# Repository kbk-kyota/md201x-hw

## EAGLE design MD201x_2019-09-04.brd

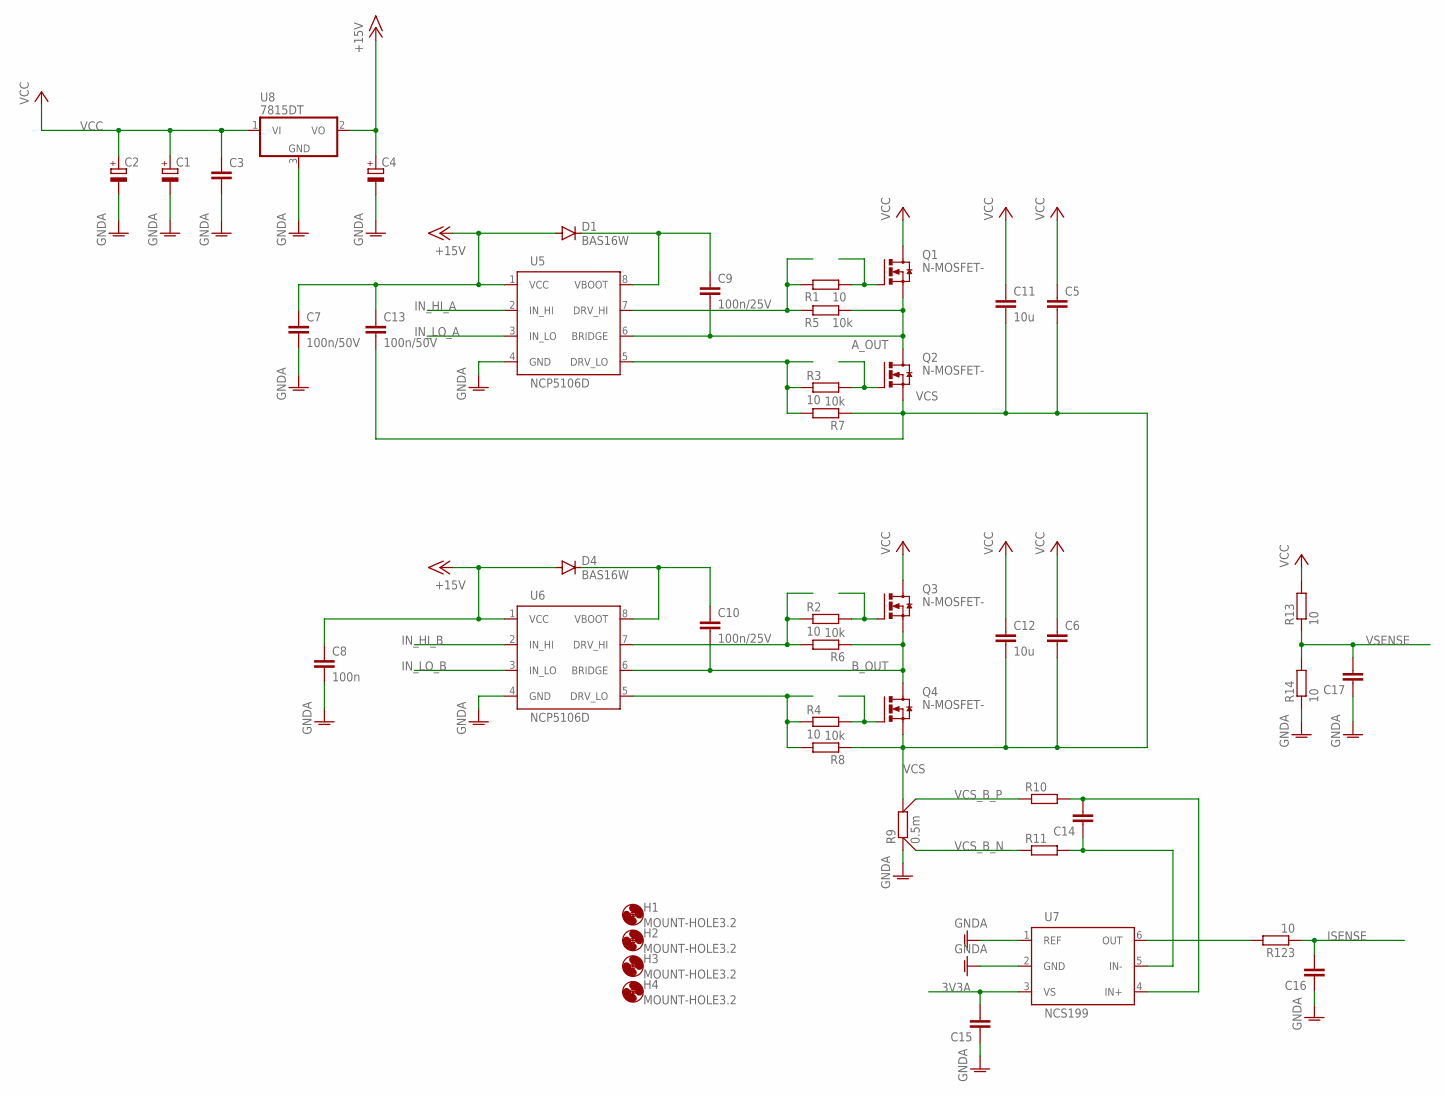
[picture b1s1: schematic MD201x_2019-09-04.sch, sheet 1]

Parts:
C1, C2: CPOL-EUE5-10.5; E5-10,5
C3, C5, C6, C14, C15, C16, C17: C-EUC0603; C0603
C4: CPOL-EUE2.5-5; E2,5-5
C7, C13: 100n/50V; C0603
C8: 100n; C0603
C9, C10: 100n/25V; C0603
C11, C12: 10u; C1210
D1, D4: BAS16W; SOD323-R
H1, H2, H3, H4: MOUNT-HOLE3.2; 3,2
Q1, Q2, Q3, Q4: N-MOSFET-; SOT669
R1, R2, R3, R4, R13, R14, R123: 10; R0603
R5, R6, R7, R8: 10k; R0603
R9: 0.5m; CSS2H-2512
R10, R11: R-EU_R0603; R0603
U5, U6: NCP5106D; SOIC127P600X175-8
U7: NCS199; SOT65P210X110-6
U8: 7815DT; TO252

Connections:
3V3A: C15.2, U7.3 (VS); also elsewhere on the board
+15V: C4.+, C7.1, C8.1, C13.1, D1.A, D4.A, U5.1 (VCC), U6.1 (VCC), U8.2 (VO); also elsewhere on the board
A_OUT: C9.2, Q1.1 (SOURCE), Q1.2 (SOURCE), Q1.3 (SOURCE), Q2.5 (DRAIN), R5.1, U5.6 (BRIDGE)
B_OUT: C10.2, Q3.1 (SOURCE), Q3.2 (SOURCE), Q3.3 (SOURCE), Q4.5 (DRAIN), R6.1, U6.6 (BRIDGE)
GNDA: C1.-, C2.-, C3.2, C4.-, C7.2, C8.2, C15.1, C16.1, C17.1, R9.1$1 (1), R9.1$2 (1), R14.1, U5.4 (GND), U6.4 (GND), U7.1 (REF), U7.2 (GND), U8.3 (GND); also elsewhere on the board
IN_HI_A: U5.2 (IN_HI); also elsewhere on the board
IN_HI_B: U6.2 (IN_HI); also elsewhere on the board
IN_LO_A: U5.3 (IN_LO); also elsewhere on the board
IN_LO_B: U6.3 (IN_LO); also elsewhere on the board
ISENSE: C16.2, R123.1; also elsewhere on the board
unnamed: R1.1, R5.2, U5.7 (DRV_HI)
unnamed: R2.1, R6.2, U6.7 (DRV_HI)
unnamed: Q1.4 (GATE), R1.2
unnamed: R4.1, R8.2, U6.5 (DRV_LO)
unnamed: R123.2, U7.6 (OUT)
unnamed: R3.1, R7.2, U5.5 (DRV_LO)
unnamed: Q3.4 (GATE), R2.2
unnamed: C14.2, R10.2, U7.4 (IN+)
unnamed: C14.1, R11.2, U7.5 (IN-)
unnamed: Q2.4 (GATE), R3.2
unnamed: Q4.4 (GATE), R4.2
unnamed: C10.1, D4.C, U6.8 (VBOOT)
unnamed: C9.1, D1.C, U5.8 (VBOOT)
VCC: C1.+, C2.+, C3.1, C5.1, C6.1, C11.1, C12.1, Q1.5 (DRAIN), Q3.5 (DRAIN), R13.2, U8.1 (VI)
VCS: C5.2, C6.2, C11.2, C12.2, C13.2, Q2.1 (SOURCE), Q2.2 (SOURCE), Q2.3 (SOURCE), Q4.1 (SOURCE), Q4.2 (SOURCE), Q4.3 (SOURCE), R7.1, R8.1, R9.2$1 (2), R9.2$2 (2)
VCS_B_N: R9.1S, R11.1
VCS_B_P: R9.2S, R10.1
VSENSE: C17.2, R13.1, R14.2; also elsewhere on the board

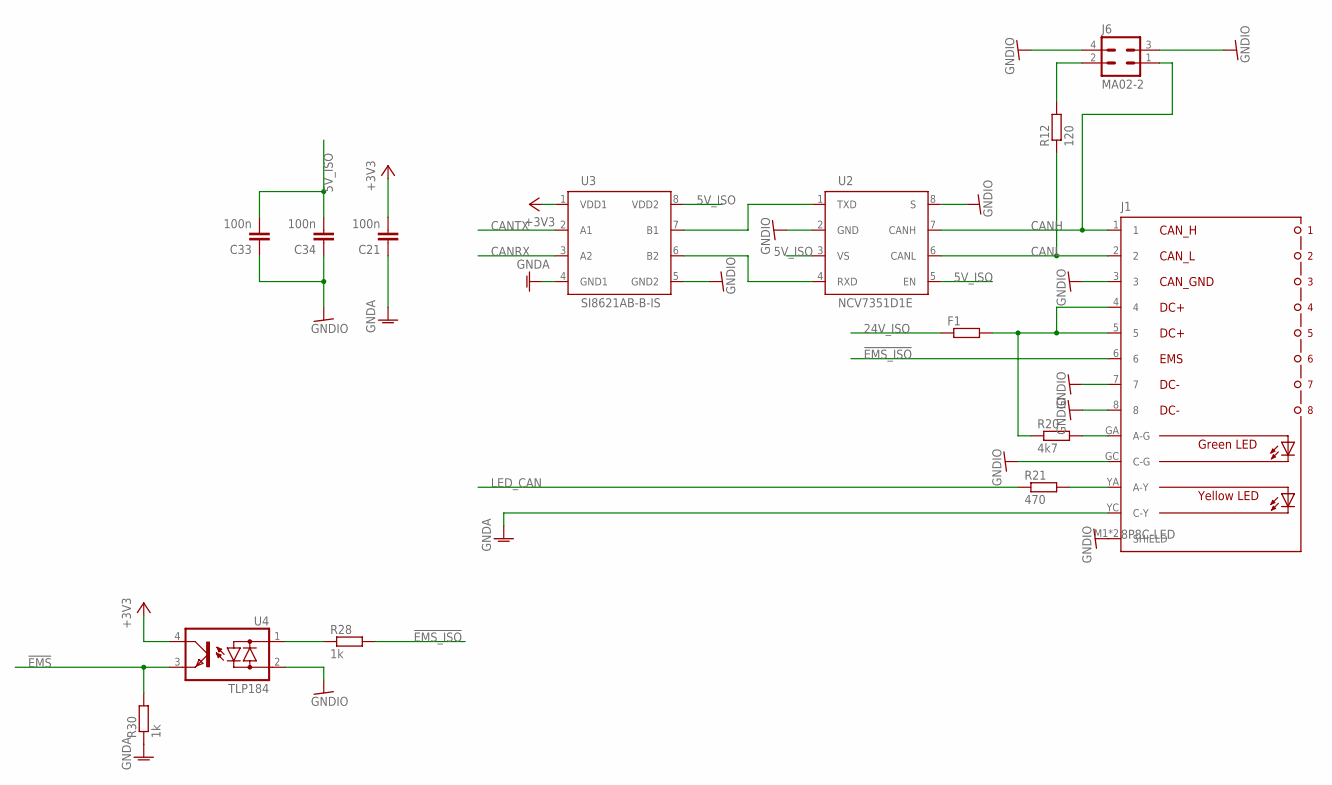
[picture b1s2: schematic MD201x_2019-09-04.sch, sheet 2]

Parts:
C21, C34: 100n; C0603
C33: 100n; C0805
F1: R-EU_R1206; R1206
J1: 8P8C-LED
J6: MA02-2; MA02-2W
R12: 120; R0603
R20: 4k7; R0603
R21: 470; R0603
R28, R30: 1k; R0603
U2: NCV7351D1E; SO08
U3: SI8621AB-B-IS; SO08
U4: TLP184; 11-4M1S

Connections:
5V_ISO: C33.2, C34.2, U2.3 (VS), U2.5 (EN), U3.8 (VDD2); also elsewhere on the board
24V_ISO: F1.1; also elsewhere on the board
!EMS: R30.2, U4.3 (E); also elsewhere on the board
!EMS_ISO: J1.6, R28.2
+3V3: C21.2, U3.1 (VDD1), U4.4 (C); also elsewhere on the board
CANH: J1.1, J6.1, U2.7 (CANH)
CANL: J1.2, R12.1, U2.6 (CANL)
CANRX: U3.3 (A2); also elsewhere on the board
CANTX: U3.2 (A1); also elsewhere on the board
GNDA: C21.1, J1.YC (C-Y), R30.1, U3.4 (GND1); also elsewhere on the board
GNDIO: C33.1, C34.1, J1.3, J1.7, J1.8, J1.GC (C-G), J1.M1 (SHIELD), J1.M2 (SHIELD), J6.3, J6.4, U2.2 (GND), U2.8 (S), U3.5 (GND2), U4.2 (AC2); also elsewhere on the board
LED_CAN: R21.1; also elsewhere on the board
unnamed: F1.2, J1.4, J1.5, R20.1
unnamed: J6.2, R12.2
unnamed: J1.GA (A-G), R20.2
unnamed: J1.YA (A-Y), R21.2
unnamed: U2.1 (TXD), U3.7 (B1)
unnamed: U2.4 (RXD), U3.6 (B2)
unnamed: R28.1, U4.1 (AC1)

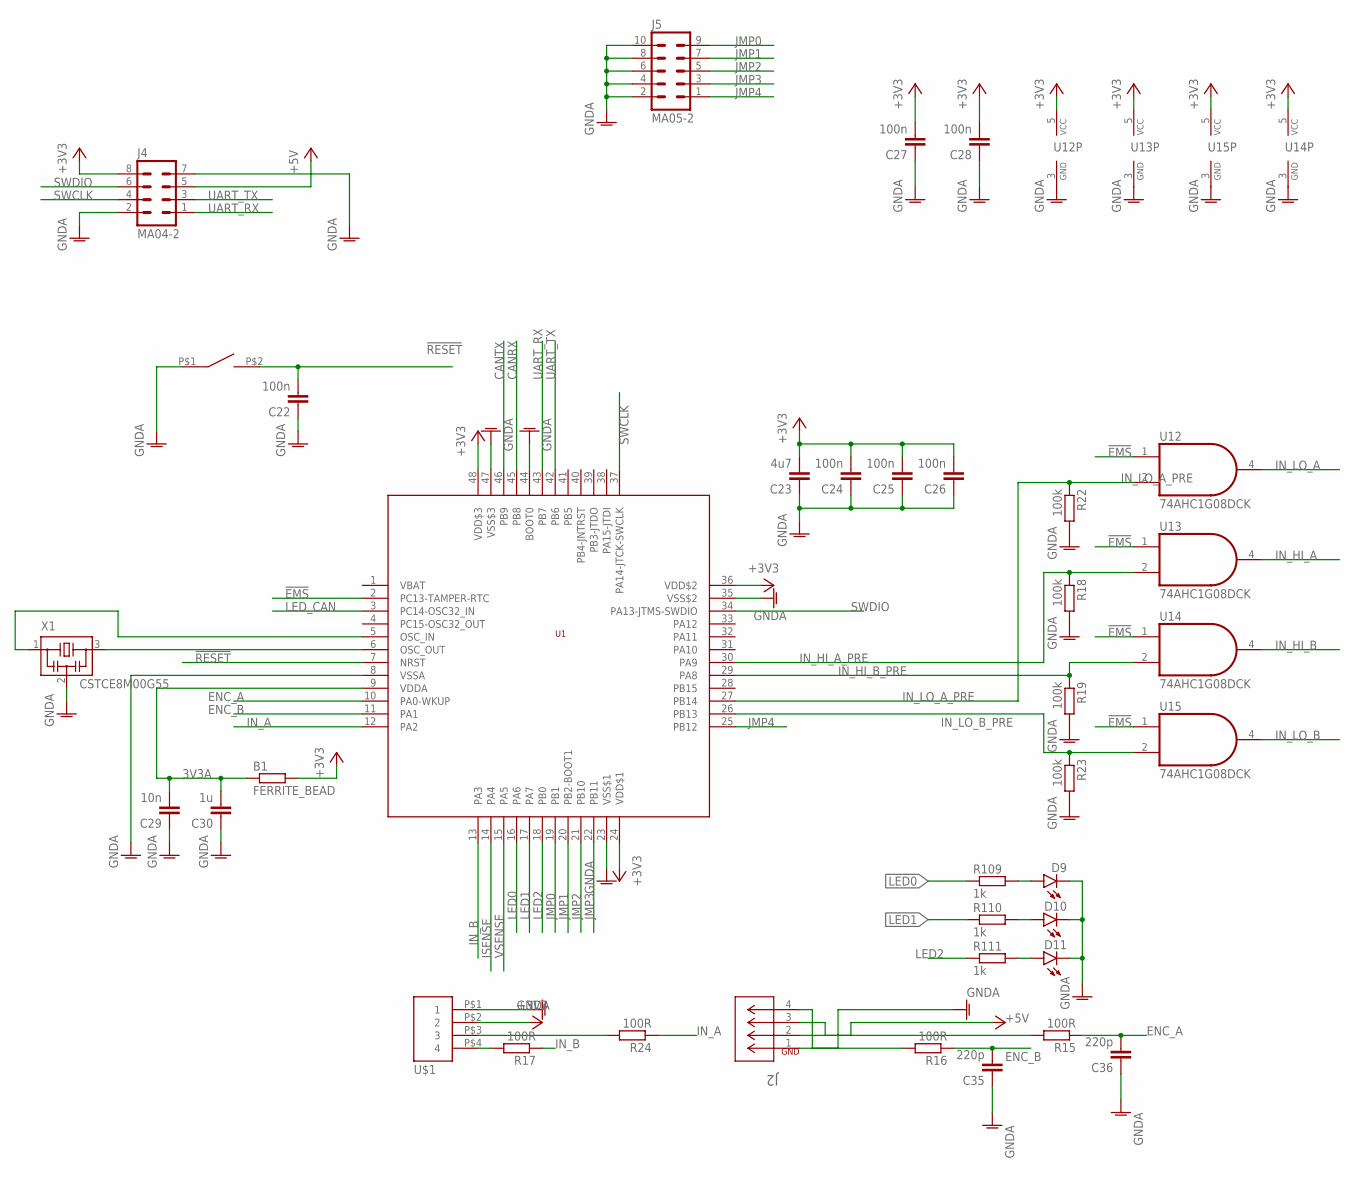
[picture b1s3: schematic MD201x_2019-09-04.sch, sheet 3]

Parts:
B1: FERRITE_BEAD; R0603
C22, C24, C25, C26, C27, C28: 100n; C0603
C23: 4u7; C0805
C29: 10n; C0603
C30: 1u; C0603
C35, C36: 220p; C0603
D9, D10, D11: LEDCHIPLED_0805; CHIPLED_0805
J2: 1744426-4; CONN4_1744426-4
J4: MA04-2; MA04-2W
J5: MA05-2; MA05-2W
R15, R16, R17, R24: 100R; R0603
R18, R19, R22, R23: 100k; R0603
R109, R110, R111: 1k; R0603
S1: SWITCH_TACTILETOP; SWITCH_TACTILE_3X6
U1: STM32F103C8; LQFP48
U12, U13, U14, U15: 74AHC1G08DCK; SC70-5
U$1: XH-4-SIDE; CON-XH-4-SIDE
X1: CSTCE8M00G55

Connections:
3V3A: B1.1, C29.2, C30.2, U1.9 (VDDA); also elsewhere on the board
!EMS: U1.2 (PC13-TAMPER-RTC), U12.1 (I0), U13.1 (I0), U14.1 (I0), U15.1 (I0); also elsewhere on the board
!RESET: C22.2, S1.P$2 (2), U1.7 (NRST)
+3V3: B1.2, C23.2, C24.2, C25.2, C26.2, C27.2, C28.2, J4.8, U1.24 (VDD$1), U1.36 (VDD$2), U1.48 (VDD$3), U12.5 (VCC), U13.5 (VCC), U14.5 (VCC), U15.5 (VCC), U$1.P$2 (2); also elsewhere on the board
+5V: J2.2, J4.5; also elsewhere on the board
CANRX: U1.45 (PB8); also elsewhere on the board
CANTX: U1.46 (PB9); also elsewhere on the board
ENC_A: C36.2, R15.1, U1.10 (PA0-WKUP)
ENC_B: C35.2, R16.1, U1.11 (PA1)
GNDA: C22.1, C23.1, C24.1, C25.1, C26.1, C27.1, C28.1, C29.1, C30.1, C35.1, C36.1, D9.C, D10.C, D11.C, J2.1, J4.2, J4.7, J5.2, J5.4, J5.6, J5.8, J5.10, R18.2, R19.2, R22.2, R23.2, S1.P$1 (1), U1.8 (VSSA), U1.23 (VSS$1), U1.35 (VSS$2), U1.44 (BOOT0), U1.47 (VSS$3), U12.3 (GND), U13.3 (GND), U14.3 (GND), U15.3 (GND), U$1.P$1 (1), X1.2; also elsewhere on the board
IN_A: R24.1, U1.12 (PA2)
IN_B: R17.1, U1.13 (PA3)
IN_HI_A: U13.4 (O); also elsewhere on the board
IN_HI_A_PRE: R18.1, U1.30 (PA9), U13.2 (I1)
IN_HI_B: U14.4 (O); also elsewhere on the board
IN_HI_B_PRE: R19.1, U1.29 (PA8), U14.2 (I1)
IN_LO_A: U12.4 (O); also elsewhere on the board
IN_LO_A_PRE: R22.1, U1.27 (PB14), U12.2 (I1)
IN_LO_B: U15.4 (O); also elsewhere on the board
IN_LO_B_PRE: R23.1, U1.26 (PB13), U15.2 (I1)
ISENSE: U1.14 (PA4); also elsewhere on the board
JMP0: J5.9, U1.19 (PB1)
JMP1: J5.7, U1.20 (PB2-BOOT1)
JMP2: J5.5, U1.21 (PB10)
JMP3: J5.3, U1.22 (PB11)
JMP4: J5.1, U1.25 (PB12)
LED0: R109.1, U1.16 (PA6)
LED1: R110.1, U1.17 (PA7)
LED2: R111.1, U1.18 (PB0)
LED_CAN: U1.3 (PC14-OSC32_IN); also elsewhere on the board
unnamed: D10.A, R110.2
unnamed: D9.A, R109.2
unnamed: U1.6 (OSC_OUT), X1.3
unnamed: J2.4, R16.2
unnamed: R17.2, U$1.P$4 (4)
unnamed: J2.3, R15.2
unnamed: R24.2, U$1.P$3 (3)
unnamed: U1.5 (OSC_IN), X1.1
unnamed: D11.A, R111.2
SWCLK: J4.4, U1.37 (PA14-JTCK-SWCLK)
SWDIO: J4.6, U1.34 (PA13-JTMS-SWDIO)
UART_RX: J4.1, U1.43 (PB7)
UART_TX: J4.3, U1.42 (PB6)
VSENSE: U1.15 (PA5); also elsewhere on the board

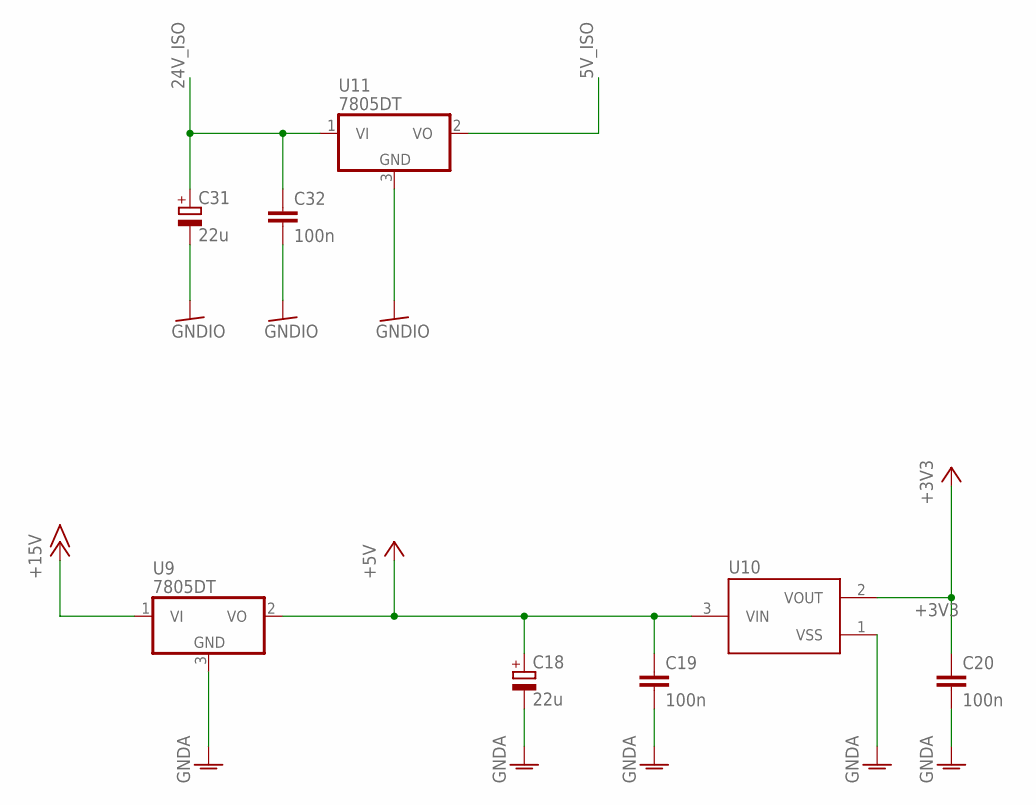
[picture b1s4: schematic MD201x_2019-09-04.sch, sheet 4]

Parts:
C18, C31: 22u; E2,5-5
C19, C20, C32: 100n; C0603
U9, U11: 7805DT; TO252
U10: XC6206; SOT95P240X110-3

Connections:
5V_ISO: U11.2 (VO); also elsewhere on the board
24V_ISO: C31.+, C32.1, U11.1 (VI); also elsewhere on the board
+3V3: C20.1, U10.2 (VOUT); also elsewhere on the board
+5V: C18.+, C19.1, U9.2 (VO), U10.3 (VIN); also elsewhere on the board
+15V: U9.1 (VI); also elsewhere on the board
GNDA: C18.-, C19.2, C20.2, U9.3 (GND), U10.1 (VSS); also elsewhere on the board
GNDIO: C31.-, C32.2, U11.3 (GND); also elsewhere on the board

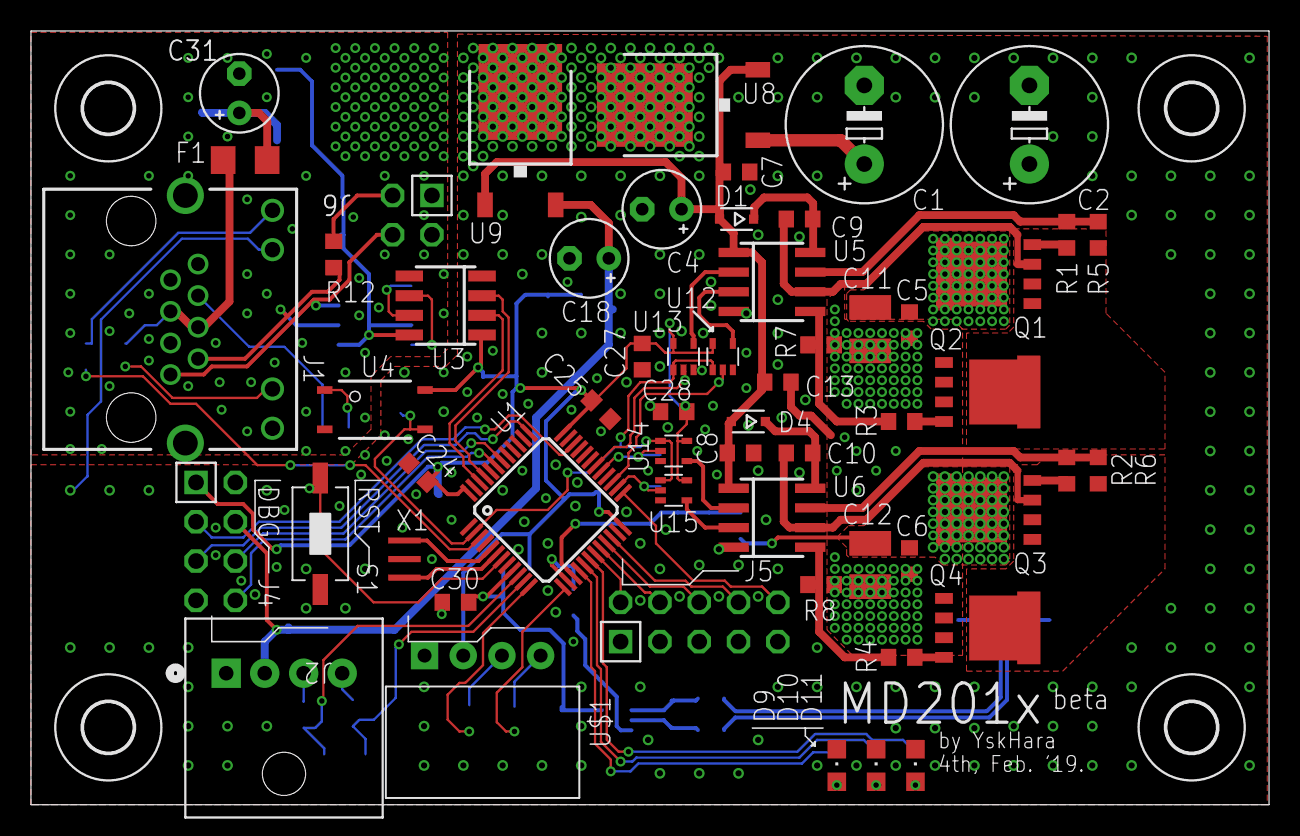
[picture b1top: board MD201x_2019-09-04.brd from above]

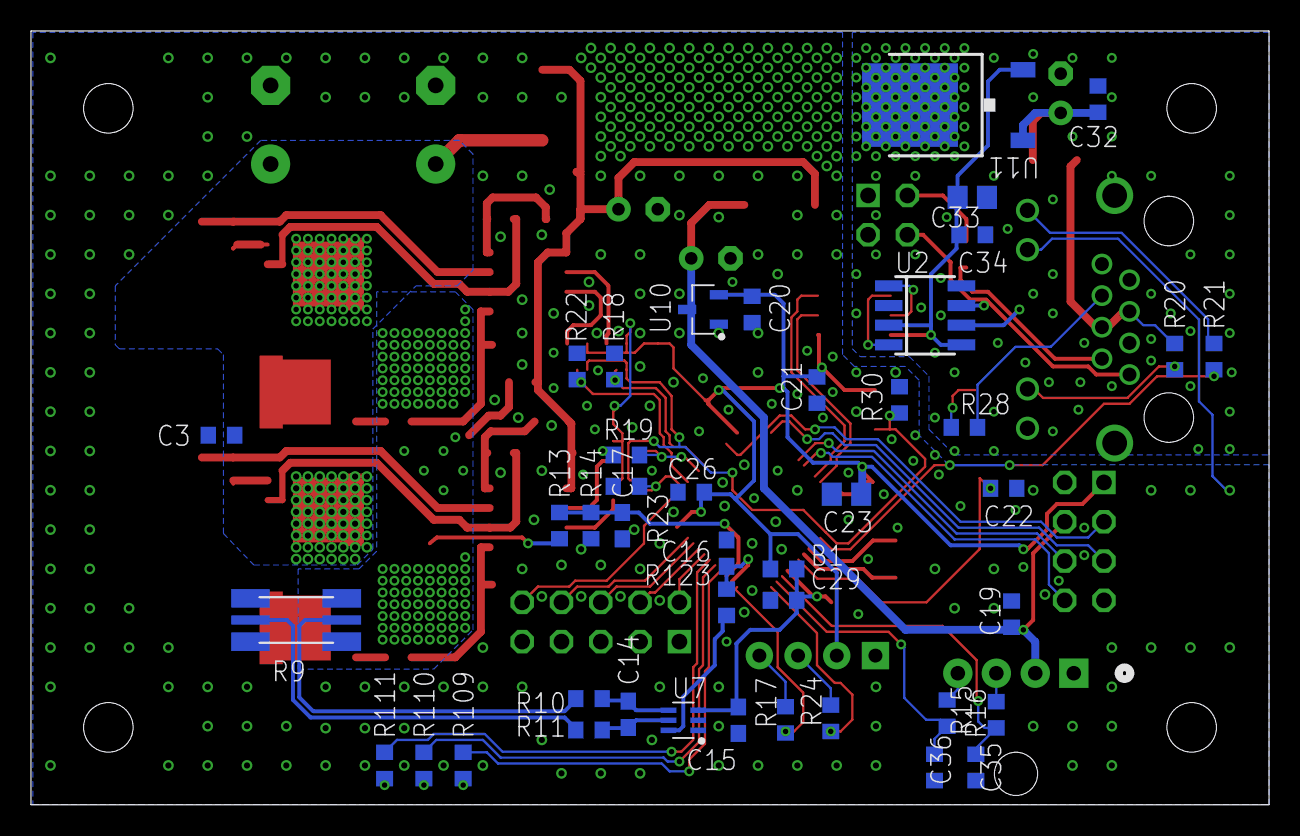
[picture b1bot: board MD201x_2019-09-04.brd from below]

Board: 2 copper layers, 80.0 x 50.0 mm, 104 parts (43 on the bottom side), 77 nets.

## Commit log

2019-09-08 エンコーダとand回路周りの修正
